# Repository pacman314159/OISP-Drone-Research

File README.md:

# 🚁 OISP Drone Research — Master Technical & System Architecture Document

> **Target Hardware Platform**: Custom Quadcopter UAV (ESP32-S3 WROOM-1 Dual-Core @ 240 MHz running FreeRTOS / ESP-IDF)  
> **Core Architecture Specs**: Hard Real-Time 500 Hz IMU Control Loop, Cascaded PID, EKF State Estimation, Zero Dynamic Allocation inside Flight Loops.  
> **Repository Location**: [d:/OneDrive_MSFT/Work/Drone_Research](file:///d:/OneDrive_MSFT/Work/Drone_Research)

---

## 📑 Master Table of Contents
- [1. Chapter 1: System Life Cycle & Finite State Machines (FSM)](#1-chapter-1-system-life-cycle--finite-state-machines-fsm)
  - [1.1 System Life Cycle Overview](#11-system-life-cycle-overview)
  - [1.2 State Transition Event Matrix](#12-state-transition-event-matrix)
  - [1.3 FSM Firmware File Registry](#13-fsm-firmware-file-registry)
  - [1.4 FSM State to RTOS Task Lifecycle Mapping](#14-fsm-state-to-rtos-task-lifecycle-mapping)
- [2. Chapter 2: Real-Time Operating System (RTOS) Architecture](#2-chapter-2-real-time-operating-system-rtos-architecture)
  - [2.1 Task Registry, Core Allocation & Priorities](#21-task-registry-core-allocation--priorities)
  - [2.2 Inter-Task Synchronization & Inter-Process Communication (IPC)](#22-inter-task-synchronization--inter-process-communication-ipc)
  - [2.3 Data Pipeline & Shared Resource Flow Diagram](#23-data-pipeline--shared-resource-flow-diagram)
  - [2.4 Shared Resource Storage & Firmware Declaration Registry](#24-shared-resource-storage--firmware-declaration-registry)
  - [2.5 Step-by-Step Task Function Execution Sequences](#25-step-by-step-task-function-execution-sequences)
- [3. Chapter 3: Firmware Architecture](#3-chapter-3-firmware-architecture)
  - [3.1 Layered Architecture Overview](#31-layered-architecture-overview)
  - [3.2 Cross-Layer Correlation & Interface Contracts](#32-cross-layer-correlation--interface-contracts)
  - [3.3 Firmware Directory & Module Registry](#33-firmware-directory--module-registry)
- [4. Chapter 4: Control System & Dynamics Architecture](#4-chapter-4-control-system--dynamics-architecture)
  - [4.1 6-DOF Quadcopter Physical Kinematics & Dynamics](#41-6-dof-quadcopter-physical-kinematics--dynamics)
  - [4.2 Mass Properties & Moment of Inertia Matrix](#42-mass-properties--moment-of-inertia-matrix)
  - [4.3 Cascaded PID Control Loop Architecture](#43-cascaded-pid-control-loop-architecture)
  - [4.4 State Estimation & Extended Kalman Filter (EKF)](#44-state-estimation--extended-kalman-filter-ekf)
  - [4.5 Control System Codebase Location Registry](#45-control-system-codebase-location-registry)
- [5. Master Cross-System Traceability Matrix](#5-master-cross-system-traceability-matrix)

---

## 1. Chapter 1: System Life Cycle & Finite State Machines (FSM)

### 1.1 System Life Cycle Overview
The operational lifecycle of the UAV from power-on until system termination is governed by a hierarchical Finite State Machine (FSM).

```mermaid
stateDiagram-v2
    [*] --> POWER_ON
    POWER_ON --> BOOT_INIT: Power Applied / Reset
    BOOT_INIT --> SENSOR_CALIBRATION: Hardware Self-Test Pass
    BOOT_INIT --> SYSTEM_ERROR: Self-Test Fail
    SENSOR_CALIBRATION --> DISARMED: Gyro/Mag Calibrated & Gyro Bias Saved
    SENSOR_CALIBRATION --> SYSTEM_ERROR: Calib Timeout / Sensor Fault
    
    state DISARMED {
        [*] --> IDLE_STANDBY
        IDLE_STANDBY --> ARMING_CHECKS: Arm Command Received (RC/GCS)
        ARMING_CHECKS --> READY_TO_ARM: All Pre-flight Checks Pass
        ARMING_CHECKS --> IDLE_STANDBY: Pre-flight Check Fail
    }
    
    DISARMED --> ARMED: Switch to ARMED State
    
    state ARMED {
        [*] --> MOTOR_SPINUP
        MOTOR_SPINUP --> IN_FLIGHT: Throttle > Min Takeoff Threshold
        IN_FLIGHT --> HOVER: Position / Altitude Hold Active
        HOVER --> IN_FLIGHT: Trajectory / Manual Command Input
    }

    ARMED --> FAILSAFE: Lost RC / Battery Low / Attitude Angle > 60°
    FAILSAFE --> LANDING: Auto-Land Protocol Triggered
    LANDING --> DISARMED: Touchdown Detected (Accel Spikes + Zero Throttle)
    ARMED --> DISARMED: Disarm Command Received
    SYSTEM_ERROR --> [*]: Hard Lockup / Safety Shutdown
```

### 1.2 State Transition Event Matrix

| Current State | Next State | Trigger Event | Trigger Source | Condition / Safeguard |
| :--- | :--- | :--- | :--- | :--- |
| `POWER_ON` | `BOOT_INIT` | Hardware Reset / Power Up | Power Supply Unit | Microcontroller VDD stable @ 3.3V |
| `BOOT_INIT` | `SENSOR_CALIBRATION` | Peripherals Initialized | Internal SW (`main.cpp`) | I2C/SPI bus scan verified |
| `BOOT_INIT` | `SYSTEM_ERROR` | Peripheral Fail | Internal SW (`main.cpp`) | MPU6050 / BMP180 not responding |
| `SENSOR_CALIBRATION` | `DISARMED` | Calibration Complete | Internal SW (`sensor_task`) | Zero gyro drift, stationary surface |
| `DISARMED` | `ARMED` | ARM Switch toggled + Throttle Low | External HW (RC Transceiver) | Pitch/Roll centered, GPS Lock ok |
| `ARMED` | `FAILSAFE` | Signal Loss > 500ms or Low Voltage | External HW / Internal SW | Batt < 10.5V or RC Watchdog timeout |
| `FAILSAFE` | `LANDING` | Failsafe Timer Expired | Internal SW (`fsm_task`) | Descend rate controlled @ 0.5 m/s |
| `LANDING` | `DISARMED` | Ground Contact Detected | Internal SW (`estimator_task`) | Accel Z impact spike + Zero throttle |

### 1.3 FSM Firmware File Registry
- **FSM State Engine Source**: [`firmware/FC_v01/src/app/flight_fsm.cpp`](file:///d:/OneDrive_MSFT/Work/Drone_Research/firmware/FC_v01/src/app)
- **FSM Definitions Header**: [`firmware/FC_v01/include/app/flight_fsm.hpp`](file:///d:/OneDrive_MSFT/Work/Drone_Research/firmware/FC_v01/include/app)
- **State Enum Declarations**: `enum class FlightState : uint8_t { BOOT_INIT, SENSOR_CALIBRATION, DISARMED, ARMED, FAILSAFE, LANDING, SYSTEM_ERROR }`

### 1.4 FSM State to RTOS Task Lifecycle Mapping

| FSM State | Active Tasks (Spawned / Running) | Suspended / Terminated Tasks | Resource Access Rights |
| :--- | :--- | :--- | :--- |
| `BOOT_INIT` | `SystemInitTask` | `ImuTask`, `AttitudeTask`, `MotorControlTask` | SPI / I2C Bus Exclusive Lock |
| `SENSOR_CALIBRATION` | `SystemInitTask`, `ImuTask`, `TelemetryTask` | `MotorControlTask`, `AttitudeTask` | Dynamic Offset Recalibration Buffer |
| `DISARMED` | `ImuTask`, `AttitudeTask`, `TelemetryTask`, `BaroTask` | `MotorControlTask` | Read-only sensors, Motors PWM 0% |
| `ARMED` | `ImuTask`, `AttitudeTask`, `MotorControlTask`, `TelemetryTask` | None | Full Control Loop & PWM Motor Outputs |
| `FAILSAFE` | `ImuTask`, `AttitudeTask`, `MotorControlTask`, `FailsafeTask` | RC Parsing Task | Auto Nav / Fixed Decent Controller |
| `SYSTEM_ERROR` | `BlinkLedTask`, `TelemetryTask` | All Control & Motor Tasks | Emergency ESC Disable (PWM 0us) |

---

## 2. Chapter 2: Real-Time Operating System (RTOS) Architecture

### 2.1 Task Registry, Core Allocation & Priorities
The firmware executes under **FreeRTOS** on the dual-core **ESP32-S3** @ 240 MHz.

| Task Identifier | Core Pinning | Task Priority | Target Frequency | Stack Size | Function Pointer Location |
| :--- | :--- | :--- | :--- | :--- | :--- |
| `ImuTask` | Core 1 | 24 (Highest) | 500 Hz (2.0 ms) | 4096 bytes | [`firmware/FC_v01/src/app/tasks.cpp`](file:///d:/OneDrive_MSFT/Work/Drone_Research/firmware/FC_v01/src/app) |
| `AttitudeTask` | Core 1 | 22 | 250 Hz (4.0 ms) | 4096 bytes | [`firmware/FC_v01/src/app/tasks.cpp`](file:///d:/OneDrive_MSFT/Work/Drone_Research/firmware/FC_v01/src/app) |
| `MotorControlTask` | Core 1 | 20 | 500 Hz (2.0 ms) | 2048 bytes | [`firmware/FC_v01/src/app/tasks.cpp`](file:///d:/OneDrive_MSFT/Work/Drone_Research/firmware/FC_v01/src/app) |
| `BaroMagTask` | Core 0 | 10 | 50 Hz (20 ms) | 3072 bytes | [`firmware/FC_v01/src/app/tasks.cpp`](file:///d:/OneDrive_MSFT/Work/Drone_Research/firmware/FC_v01/src/app) |
| `TelemetryTask` | Core 0 | 5 | 20 Hz (50 ms) | 4096 bytes | [`firmware/FC_v01/src/telemetry/`](file:///d:/OneDrive_MSFT/Work/Drone_Research/firmware/FC_v01/src/telemetry) |

### 2.2 Inter-Task Synchronization & Inter-Process Communication (IPC)
- **Direct Task Notifications**: Used for high-speed zero-latency signaling from IMU ISR to `ImuTask`.
- **Mutexes**:
  - `g_i2c_bus_mutex`: Prevents concurrent bus collisions between `ImuTask` and `BaroMagTask`.
  - `g_state_mutex`: Guards access to global telemetry and system state structs.
- **Ring Buffers / Queues**:
  - `g_imu_queue`: Lock-free SCMC (Single Producer, Single Consumer) queue transferring 6-axis raw values to `AttitudeTask`.

### 2.3 Data Pipeline & Shared Resource Flow Diagram

```mermaid
flowchart TD
    subgraph Core1 ["Core 1: High-Speed Flight Control Loop (500 Hz / 250 Hz)"]
        HW_MPU["Hardware MPU6050 (I2C/SPI)"] -->|Interrupt ISR| TSK_IMU["ImuTask (500 Hz)"]
        TSK_IMU -->|Raw Accel/Gyro Data| BUF_IMU[("g_imu_data_buffer (Protected by RingBuffer)")]
        BUF_IMU --> TSK_ATT["AttitudeTask (250 Hz / Cascaded PID)"]
        TSK_ATT -->|Motor PWM Signals| HW_ESC["Hardware ESCs (MCPWM / RMT)"]
    end

    subgraph Core0 ["Core 0: Low-Priority Navigation & Telemetry (50 Hz / 20 Hz)"]
        HW_BMP["BMP180 Baro"] --> TSK_NAV["BaroMagTask (50 Hz)"]
        TSK_NAV -->|Alt / Mag Data| BUF_NAV[("g_nav_data_buffer (Mutex: g_state_mutex)")]
        BUF_NAV --> TSK_TEL["TelemetryTask (20 Hz)"]
        TSK_TEL -->|Radio Packets| HW_RADIO["LoRa Ra-02 / NRF24L01+ / BLE"]
    end
```

### 2.4 Shared Resource Storage & Firmware Declaration Registry
- **Global Data Structures**: Defined in [`firmware/FC_v01/include/middleware/shared_resources.hpp`](file:///d:/OneDrive_MSFT/Work/Drone_Research/firmware/FC_v01/include/middleware)
- **Shared Variables**:
  - `IMUData g_imu_data; // Gyro (dps), Accel (m/s^2)`
  - `AttitudeData g_attitude; // Roll, Pitch, Yaw (radians)`
  - `MotorCommand g_motor_cmd; // PWM outputs (1000 - 2000 us)`
- **Zero Dynamic Memory Rule**: All mutexes (`StaticSemaphore_t`), queues (`xQueueCreateStatic`), and task stacks are statically instantiated at compile time.

### 2.5 Step-by-Step Task Function Execution Sequences

#### `ImuTask` Execution Flow (Loop Period: 2.0 ms)
1. **Step 1**: Block waiting for Direct Task Notification from MPU6050 INT pin ISR (`ulTaskNotifyTake`).
2. **Step 2**: Acquire `g_i2c_bus_mutex` with a 1 ms timeout.
3. **Step 3**: Execute burst read of 14 bytes from MPU6050 registers (Accel X, Y, Z, Temp, Gyro X, Y, Z).
4. **Step 4**: Release `g_i2c_bus_mutex`.
5. **Step 5**: Apply sensor calibration scale/offset matrices: $\mathbf{a}_{\text{corr}} = \mathbf{K}_a (\mathbf{a}_{\text{raw}} - \mathbf{b}_a)$.
6. **Step 6**: Push structured `IMUData` packet into `g_imu_queue` and unblock `AttitudeTask`.

---

## 3. Chapter 3: Firmware Architecture

### 3.1 Layered Architecture Overview
The firmware is structured into clean modular layers, adhering to strict single-direction dependency flows (Upper layers depend on lower layers, lower layers never include upper layers).

```
+-------------------------------------------------------------------+
| 5. Application Layer (flight_fsm, mission_manager, safety)        |
+-------------------------------------------------------------------+
| 4. Control Layer (cascaded_pid, rate_controller, attitude_ctrl)   |
+-------------------------------------------------------------------+
| 3. Estimator Layer (ekf_sensor_fusion, complementary_filter)      |
+-------------------------------------------------------------------+
| 2. Middleware Layer (shared_resources, ring_buffer, rtos_wrappers)|
+-------------------------------------------------------------------+
| 1. Drivers & Platform HAL (mpu6050, bmp180, i2c_master, mcpwm)     |
+-------------------------------------------------------------------+
```

### 3.2 Cross-Layer Correlation & Interface Contracts

| Driver Module | Platform HAL Interface | Upper Middleware Data Producer | Consuming Control Module |
| :--- | :--- | :--- | :--- |
| `mpu6050_driver.cpp` | `esp_i2c_master.c` | `g_imu_queue` | `cascaded_pid.cpp` |
| `bmp180_driver.cpp` | `esp_i2c_master.c` | `g_baro_queue` | `altitude_kalman.cpp` |
| `esc_driver.cpp` | `esp_mcpwm_hal.c` | `g_motor_cmd` | Direct Hardware Actuators |
| `lora_ra02_driver.cpp`| `esp_spi_master.c` | `g_telemetry_queue` | `ground_station_link.cpp` |

### 3.3 Firmware Directory & Module Registry
- **Root Firmware Directory**: [`firmware/FC_v01/`](file:///d:/OneDrive_MSFT/Work/Drone_Research/firmware/FC_v01)
  - `src/app/`: Application state logic and RTOS task definitions.
  - `src/control/`: Inner-loop rate PID, outer-loop attitude PID implementations.
  - `src/estimators/`: EKF 9-DOF / 6-DOF sensor fusion state estimation.
  - `src/drivers/`: Hardware driver implementations for MPU6050, BMP180, HMC5883L, ESC PWM.
  - `src/platforms/`: ESP32-S3 ESP-IDF peripheral hardware abstraction wrapper layer.
  - `src/middleware/`: RTOS IPC primitives, ring buffers, and thread-safe data accessors.

---

## 4. Chapter 4: Control System & Dynamics Architecture

### 4.1 6-DOF Quadcopter Physical Kinematics & Dynamics
The flight dynamics are modeled using 6-DOF rigid body Newton-Euler equations expressed in the Body Frame $B$ relative to the Inertial Earth Frame $N$.

$$\begin{aligned}
\dot{\mathbf{p}}^N &= \mathbf{v}^N \\
\dot{\mathbf{v}}^N &= \frac{1}{m} \mathbf{R}_B^N \mathbf{F}^B - \begin{bmatrix} 0 \\ 0 \\ g \end{bmatrix} \\
\dot{\mathbf{R}}_B^N &= \mathbf{R}_B^N \boldsymbol{\Omega}_\times \\
\mathbf{I} \dot{\boldsymbol{\omega}}^B &= \boldsymbol{\tau}^B - \boldsymbol{\omega}^B \times (\mathbf{I} \boldsymbol{\omega}^B)
\end{aligned}$$

Where:
- $\mathbf{p}^N = [x, y, z]^T$: Inertial position (m)
- $\mathbf{v}^N = [v_x, v_y, v_z]^T$: Velocity vector (m/s)
- $\mathbf{R}_B^N$: Rotation matrix from Body frame to Earth frame
- $\boldsymbol{\omega}^B = [p, q, r]^T$: Body angular rates (rad/s)
- $\mathbf{F}^B = [0, 0, \sum T_i]^T$: Total thrust generated by BLDC motors (N)
- $\boldsymbol{\tau}^B = [\tau_\phi, \tau_\theta, \tau_\psi]^T$: Roll, Pitch, and Yaw moments (N·m)

### 4.2 Mass Properties & Moment of Inertia Matrix
Derived from CAD model assemblies ([`3d_models/Full_body/`](file:///d:/OneDrive_MSFT/Work/Drone_Research/3d_models/Full_body)):

$$\mathbf{I} = \begin{bmatrix} I_{xx} & 0 & 0 \\ 0 & I_{yy} & 0 \\ 0 & 0 & I_{zz} \end{bmatrix} = \begin{bmatrix} 0.0142 & 0 & 0 \\ 0 & 0.0142 & 0 \\ 0 & 0 & 0.0285 \end{bmatrix} \text{kg}\cdot\text{m}^2$$

### 4.3 Cascaded PID Control Loop Architecture

```mermaid
flowchart LR
    SP["Desired Attitude (Roll, Pitch, Yaw)"] --> SUM1(("+"))
    SUM1 -->|Angle Error| PID_ANG["Angle PID Controller (100 Hz)"]
    PID_ANG -->|Desired Angular Rate| SUM2(("+"))
    IMU_ATT["Attitude Estimator (EKF / Complementary)"] -->|"-"| SUM1
    
    SUM2 -->|Rate Error| PID_RATE["Rate PID Controller (500 Hz)"]
    IMU_GYRO["IMU Gyroscope (500 Hz)"] -->|"-"| SUM2
    
    PID_RATE -->|Control Torque τ| MIXER["Motor Mixer Matrix"]
    MIXER -->|Motor Speeds ω1..4| ESC["ESC / BLDC Motors"]
```

#### Motor Control Mixer Equation ($X$-Configuration Quadcopter)
$$\begin{bmatrix} u_1 \\ u_2 \\ u_3 \\ u_4 \end{bmatrix} = \begin{bmatrix} 1 & -1 & 1 & 1 \\ 1 & -1 & -1 & -1 \\ 1 & 1 & -1 & 1 \\ 1 & 1 & 1 & -1 \end{bmatrix} \begin{bmatrix} T_{\text{coll}} \\ \tau_\phi \\ \tau_\theta \\ \tau_\psi \end{bmatrix}$$

### 4.4 State Estimation & Extended Kalman Filter (EKF)
State Vector ($\mathbf{x} \in \mathbb{R}^7$):
$$\mathbf{x} = \begin{bmatrix} q_0 & q_1 & q_2 & q_3 & b_{gx} & b_{gy} & b_{gz} \end{bmatrix}^T$$

- **Predict Step**: $\hat{\mathbf{x}}_{k|k-1} = f(\hat{\mathbf{x}}_{k-1}, \mathbf{u}_k)$
- **Covariance Predict**: $\mathbf{P}_{k|k-1} = \mathbf{F}_k \mathbf{P}_{k-1} \mathbf{F}_k^T + \mathbf{Q}_k$
- **Kalman Gain**: $\mathbf{K}_k = \mathbf{P}_{k|k-1} \mathbf{H}_k^T (\mathbf{H}_k \mathbf{P}_{k|k-1} \mathbf{H}_k^T + \mathbf{R}_k)^{-1}$
- **Update Step**: $\hat{\mathbf{x}}_{k|k} = \hat{\mathbf{x}}_{k|k-1} + \mathbf{K}_k (\mathbf{z}_k - h(\hat{\mathbf{x}}_{k|k-1}))$

### 4.5 Control System Codebase Location Registry
- **Cascaded PID Class**: [`firmware/FC_v01/src/control/cascaded_pid.cpp`](file:///d:/OneDrive_MSFT/Work/Drone_Research/firmware/FC_v01/src/control)
- **Motor Mixer Matrix**: [`firmware/FC_v01/src/control/motor_mixer.cpp`](file:///d:/OneDrive_MSFT/Work/Drone_Research/firmware/FC_v01/src/control)
- **EKF Math & Matrix Library**: [`firmware/EKF-sensor-fusion/test/EKF.cpp`](file:///d:/OneDrive_MSFT/Work/Drone_Research/firmware/EKF-sensor-fusion/test)
- **Signal Analyzers (Python)**: [`analyzers/imu_fft.py`](file:///d:/OneDrive_MSFT/Work/Drone_Research/analyzers)

---

## 5. Master Cross-System Traceability Matrix

This matrix establishes unambiguous links across FSM States, RTOS Tasks, Firmware Modules, Data Buffers, and Control/Physics Formulations.

| FSM State ID | Active RTOS Task | Firmware Layer & Path | Shared Resource / Buffer | Math / Physics Reference |
| :--- | :--- | :--- | :--- | :--- |
| `BOOT_INIT` | `SystemInitTask` | [`src/app/main.cpp`](file:///d:/OneDrive_MSFT/Work/Drone_Research/firmware/FC_v01/src/main.cpp) | `g_i2c_bus_mutex` | Hardware Register Specs |
| `SENSOR_CALIBRATION` | `ImuTask` | [`src/drivers/mpu6050.cpp`](file:///d:/OneDrive_MSFT/Work/Drone_Research/firmware/FC_v01/src/drivers) | `g_imu_calib_buffer` | Accel/Gyro Bias $\mathbf{b}_a, \mathbf{b}_g$ |
| `DISARMED` | `BaroMagTask` | [`src/drivers/bmp180.cpp`](file:///d:/OneDrive_MSFT/Work/Drone_Research/firmware/FC_v01/src/drivers) | `g_nav_data_buffer` | Barometric Formula $h = f(P)$ |
| `ARMED` | `ImuTask` (500Hz) | [`src/app/tasks.cpp`](file:///d:/OneDrive_MSFT/Work/Drone_Research/firmware/FC_v01/src/app) | `g_imu_queue` | Rate Loop Gyro $\boldsymbol{\omega}^B$ |
| `ARMED` | `AttitudeTask` (250Hz)| [`src/control/cascaded_pid.cpp`](file:///d:/OneDrive_MSFT/Work/Drone_Research/firmware/FC_v01/src/control) | `g_motor_cmd` | Cascaded PID & Mixer Matrix |
| `FAILSAFE` | `FailsafeTask` | [`src/app/flight_fsm.cpp`](file:///d:/OneDrive_MSFT/Work/Drone_Research/firmware/FC_v01/src/app) | `g_failsafe_state` | Descent Dynamics $\dot{z} = -0.5\text{m/s}$ |

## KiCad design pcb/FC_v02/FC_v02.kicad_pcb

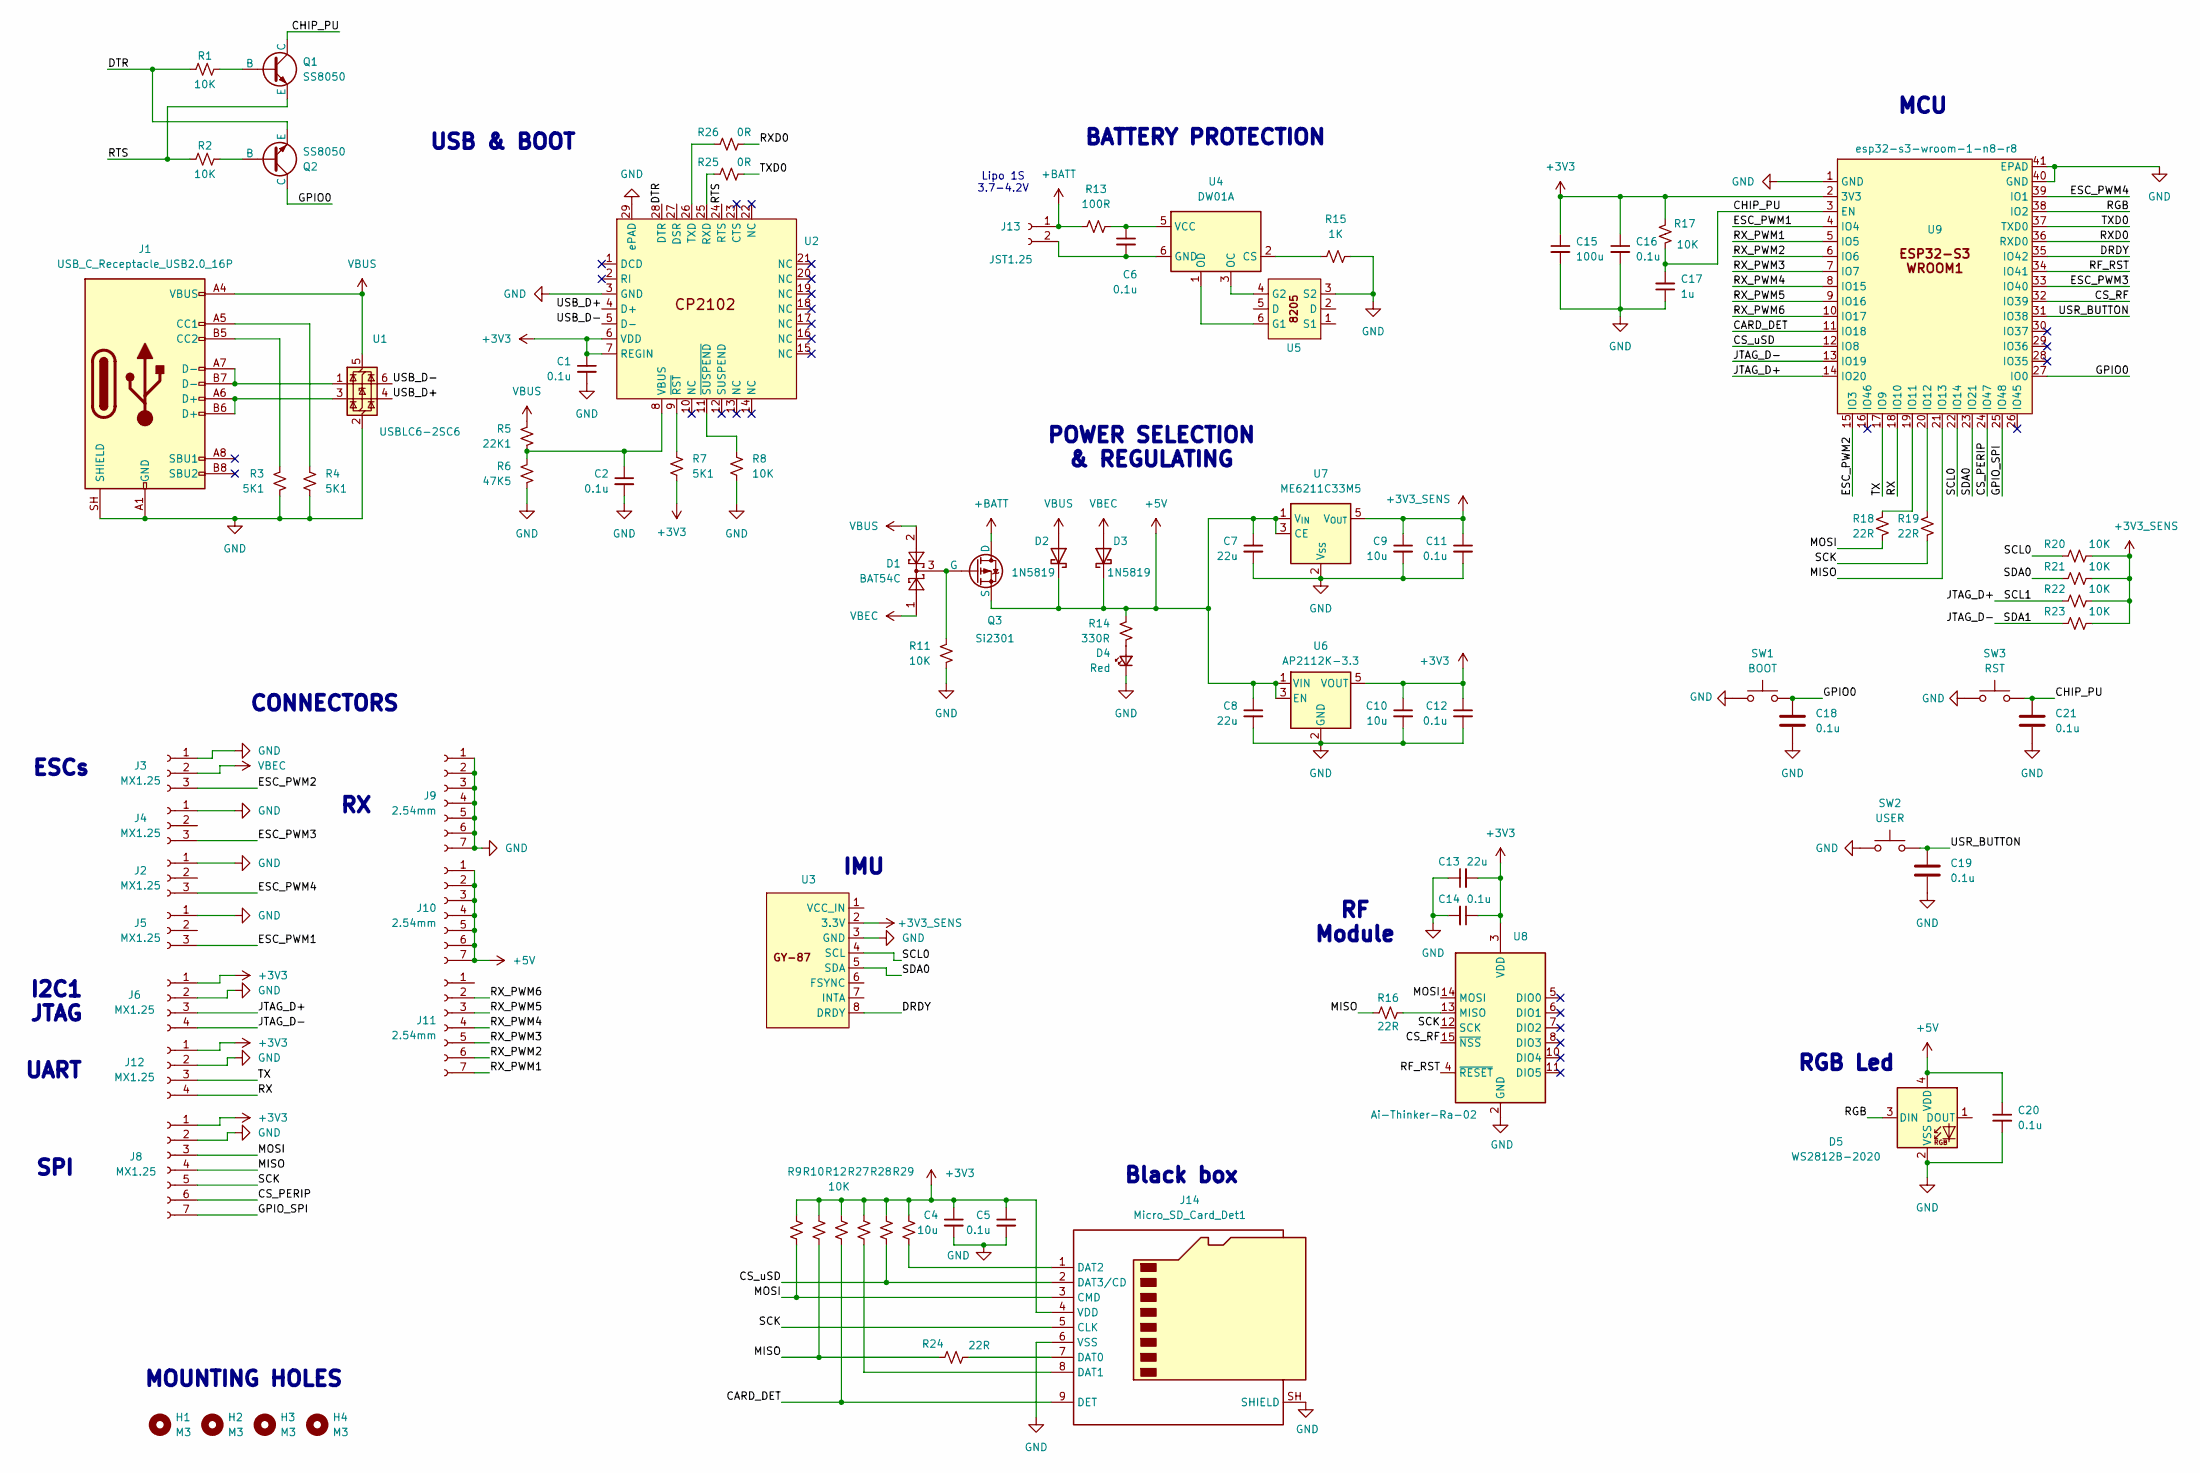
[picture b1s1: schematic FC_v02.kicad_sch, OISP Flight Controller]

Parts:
C1, C2, C5, C6, C11, C12, C14, C16, C18, C19, C20, C21: 0.1u; C_0603_1608Metric
C4, C9, C10: 10u; C_0805_2012Metric
C7, C8: 22u; CP_EIA-3216-10_Kemet-I
C13: 22u; C_0805_2012Metric
C15: 100u; CP_EIA-3216-10_Kemet-I
C17: 1u; C_0603_1608Metric
D1: BAT54C; SOT-23
D2, D3: 1N5819; D_SOD-123
D4: Red; LED_0805_2012Metric
D5: WS2812B-2020; LED_WS2812B-2020_PLCC4_2.0x2.0mm
H1, H2, H3, H4: M3; MountingHole_3.2mm_M3_DIN965_Pad
J1: USB_C_Receptacle_USB2.0_16P; USB_C_Receptacle_GCT_USB4105-xx-A_16P_TopMnt_Horizontal
J2, J3, J4, J5: MX1.25; MX_1.25mm_RA_SMD_3P
J6, J12: MX1.25; MX_1.25mm_RA_SMD_4P
J8: MX1.25; MX_1.25mm_RA_SMD_8P
J9, J10, J11: 2.54mm; _PinSocket_1x07_P2.54mm_Vertical
J13: JST1.25; MX_1.25mm_RA_SMD_2P
J14: Micro_SD_Card_Det1; Micro_SD_Card_Socket
Q1, Q2: SS8050; SOT-23
Q3: Si2301; SOT-23
R1, R2, R8, R9, R10, R11, R12, R17, R20, R21, R22, R23, R27, R28, R29: 10K; R_0603_1608Metric
R3, R4, R7: 5K1; R_0603_1608Metric
R5: 22K1; R_0603_1608Metric
R6: 47K5; R_0603_1608Metric
R13: 100R; R_0603_1608Metric
R14: 330R; R_0603_1608Metric
R15: 1K; R_0603_1608Metric
R16, R18, R19, R24: 22R; R_0603_1608Metric
R25, R26: 0R; R_0603_1608Metric
SW1: BOOT; SW_Push_3x4x2.5mm
SW2: USER; SW_Push_3x4x2.5mm
SW3: RST; SW_Push_3x4x2.5mm
U1: USBLC6-2SC6; SOT-23-6
U2: CP2102; QFN-28-1EP_5x5mm_P0.5mm_EP3.25x3.25mm_ThermalVias
U3: GY-87
U4: DW01A; SOT-23-6
U5: 8205; TSOT-23-6
U6: AP2112K-3.3; SOT-23-5
U7: ME6211C33M5; SOT-23-5
U8: Ai-Thinker-Ra-02; Ai-Thinker-Ra-01-LoRa
U9: esp32-s3-wroom-1-n8-r8; ESP32-S3-WROOM-1

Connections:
+3V3: C1.1, C4.1, C5.1, C10.1, C12.1, C13.2, C14.1, C15.1, C16.1, J6.1, J8.1, J12.1, J14.4 (VDD), R7.2, R9.1, R10.1, R12.1, R17.1, R27.1, R28.1, R29.1, U2.6 (VDD), U2.7 (REGIN), U6.5 (VOUT), U8.3 (VDD), U9.2 (3V3)
+3V3_SENS: C9.1, C11.1, R20.2, R21.2, R22.2, R23.2, U3.2 (3.3V), U7.5 (V_{OUT})
+5V: C7.1, C8.1, C20.1, D2.1 (K), D3.1 (K), D5.4 (VDD), J10.1, J10.2, J10.3, J10.4, J10.5, J10.6, J10.7, Q3.2 (S), R14.2, U6.1 (VIN), U6.3 (EN), U7.1 (V_{IN}), U7.3 (CE)
+BATT: J13.1, Q3.3 (D), R13.1
/CARD_DET: J14.9 (DET), R12.2, U9.11 (IO18)
/CHIP_PU: C17.2, C21.1, Q1.3 (C), R17.2, SW3.2, U9.3 (EN)
/CS_PERIP: J8.6, U9.24 (IO47)
/CS_RF: U8.15 (~NSS), U9.32 (IO39)
/CS_uSD: J14.2 (DAT3/CD), R28.2, U9.12 (IO8)
/DRDY: U3.8 (DRDY), U9.35 (IO42)
/DTR: Q2.2 (E), R1.1, U2.28 (DTR)
/ESC_PWM1: J5.3, U9.4 (IO4)
/ESC_PWM2: J3.3, U9.15 (IO3)
/ESC_PWM3: J4.3, U9.33 (IO40)
/ESC_PWM4: J2.3, U9.39 (IO1)
/GPIO0: C18.1, Q2.3 (C), SW1.2, U9.27 (IO0)
/GPIO_SPI: J8.7, U9.25 (IO48)
/JTAG_D+: J6.3, R22.1, U9.14 (IO20)
/JTAG_D-: J6.4, R23.1, U9.13 (IO19)
/MISO: J8.4, R10.2, R16.1, R24.1, U9.21 (IO13)
/MOSI: J8.3, J14.3 (CMD), R9.2, R18.2, U8.14 (MOSI)
/RF_RST: U8.4 (~RESET), U9.34 (IO41)
/RGB: D5.3 (DIN), U9.38 (IO2)
/RTS: Q1.2 (E), R2.1, U2.24 (RTS)
/RX: J12.4, U9.18 (IO10)
/RXD0: R26.2, U9.36 (RXD0)
/RX_PWM1: J11.7, U9.5 (IO5)
/RX_PWM2: J11.6, U9.6 (IO6)
/RX_PWM3: J11.5, U9.7 (IO7)
/RX_PWM4: J11.4, U9.8 (IO15)
/RX_PWM5: J11.3, U9.9 (IO16)
/RX_PWM6: J11.2, U9.10 (IO17)
/SCK: J8.5, J14.5 (CLK), R19.2, U8.12 (SCK)
/SCL0: R20.1, U3.4 (SCL), U9.22 (IO14)
/SDA0: R21.1, U3.5 (SDA), U9.23 (IO21)
/TX: J12.3, U9.17 (IO9)
/TXD0: R25.2, U9.37 (TXD0)
/USB_D+: U1.4 (I/O2), U2.4 (D+)
/USB_D-: U1.6 (I/O1), U2.5 (D-)
/USR_BUTTON: C19.1, SW2.2, U9.31 (IO38)
GND: C1.2, C2.2, C4.2, C5.2, C7.2, C8.2, C9.2, C10.2, C11.2, C12.2, C13.1, C14.2, C15.2, C16.2, C17.1, C18.2, C19.2, C20.2, C21.2, D4.1 (K), D5.2 (VSS), J1.A1 (GND), J1.A12 (GND), J1.B1 (GND), J1.B12 (GND), J1.SH (SHIELD), J2.1, J3.1, J4.1, J5.1, J6.2, J8.2, J9.1, J9.2, J9.3, J9.4, J9.5, J9.6, J9.7, J12.2, J14.6 (VSS), J14.SH (SHIELD), R3.2, R4.2, R6.2, R8.2, R11.1, R15.2, SW1.1, SW2.1, SW3.1, U1.2 (GND), U2.3 (GND), U2.29 (ePAD), U3.3 (GND), U5.3 (S2), U6.2 (GND), U7.2 (V_{SS}), U8.1 (GND), U8.2 (GND), U8.9 (GND), U8.16 (GND), U9.1 (GND), U9.40 (GND), U9.41 (EPAD)
unnamed: D4.2 (A), R14.1
unnamed: J1.A5 (CC1), R4.1
unnamed: J1.B5 (CC2), R3.1
unnamed: J1.A6 (D+), J1.B6 (D+), U1.3 (I/O2)
unnamed: J1.A7 (D-), J1.B7 (D-), U1.1 (I/O1)
unnamed: C6.2, J13.2, U4.6 (GND)
unnamed: J14.7 (DAT0), R24.2
unnamed: J14.8 (DAT1), R27.2
unnamed: J14.1 (DAT2), R29.2
unnamed: Q1.1 (B), R1.2
unnamed: Q2.1 (B), R2.2
unnamed: D1.3, Q3.1 (G), R11.2
unnamed: R25.1, U2.25 (RXD)
unnamed: R26.1, U2.26 (TXD)
unnamed: C2.1, R5.2, R6.1, U2.8 (VBUS)
unnamed: R7.1, U2.9 (~RST)
unnamed: R8.1, U2.11 (~SUSPEND)
unnamed: R15.1, U4.2 (CS)
unnamed: U4.3 (OC), U5.4 (G2)
unnamed: U4.1 (OD), U5.6 (G1)
unnamed: C6.1, R13.2, U4.5 (VCC)
unnamed: R16.2, U8.13 (MISO)
unnamed: R18.1, U9.19 (IO11)
unnamed: R19.1, U9.20 (IO12)
VBEC: D1.1, D3.2 (A), J3.2
VBUS: D1.2, D2.2 (A), J1.A4 (VBUS), J1.A9 (VBUS), J1.B4 (VBUS), J1.B9 (VBUS), R5.1, U1.5 (VBUS)

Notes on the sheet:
RF Module
ESCs
IMU
RGB Led
Black box
MCU
POWER SELECTION & REGULATING
USB & BOOT
Lipo 1S 3.7-4.2V
BATTERY PROTECTION
CONNECTORS
MOUNTING HOLES
SPI
I2C1 JTAG
UART

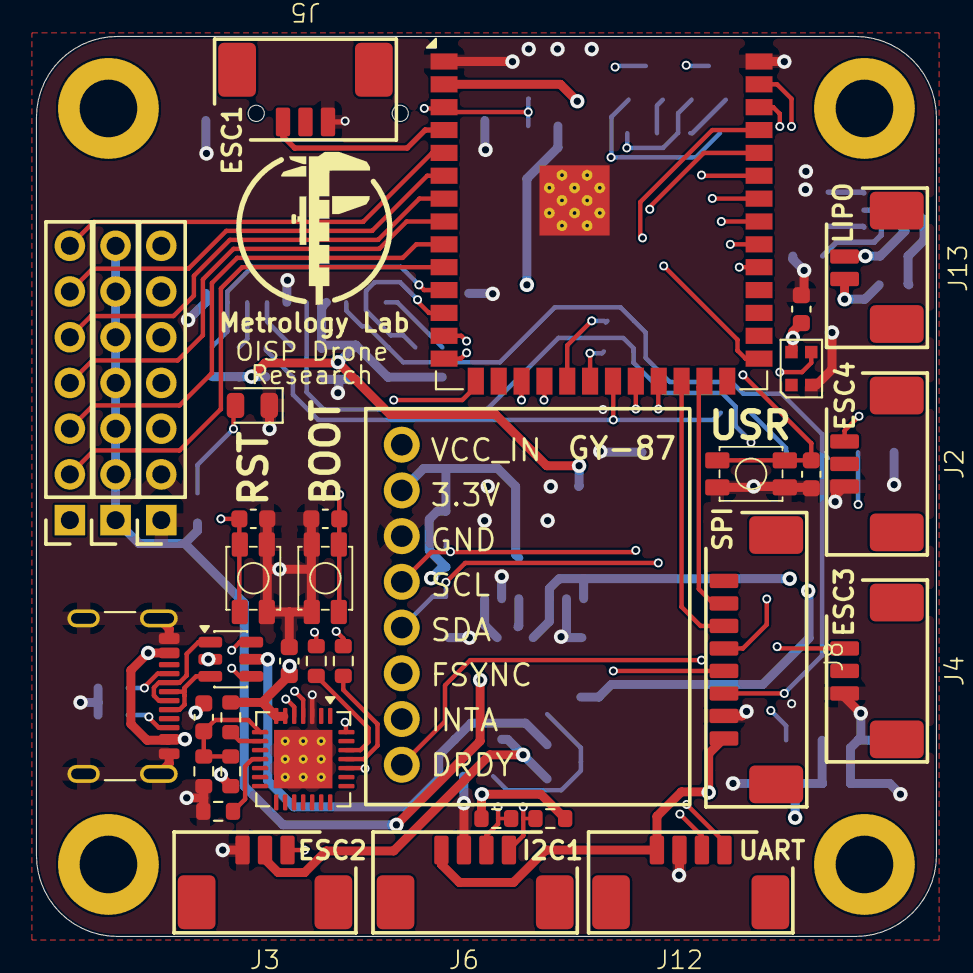
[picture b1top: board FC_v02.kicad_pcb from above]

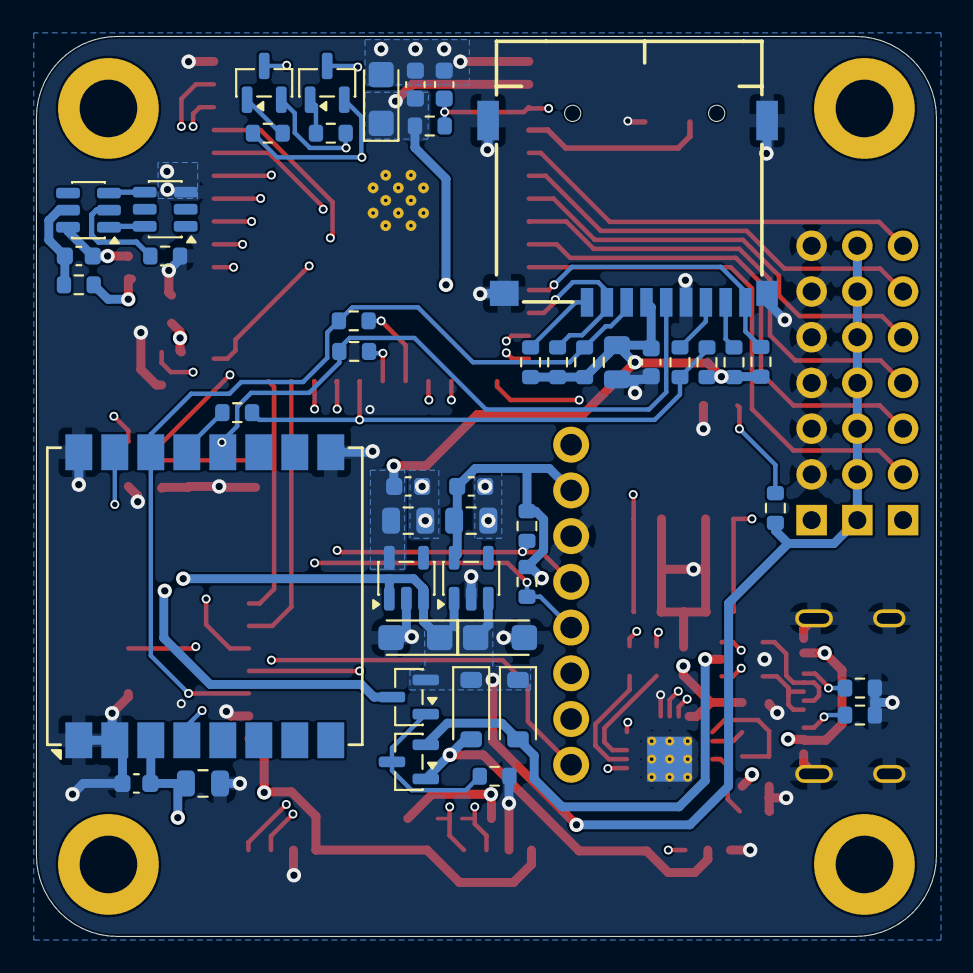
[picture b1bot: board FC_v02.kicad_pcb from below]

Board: 4 copper layers, 50.0 x 50.0 mm, 86 parts (47 on the bottom side), 67 nets.

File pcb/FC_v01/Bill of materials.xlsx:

Reference | Qty | Value | Footprint | Unit price | Unit total | Description | Supplier
C1 | 1 | 1u | Capacitor_SMD:C_0402_1005Metric
C2,C3,C5,C6,C11,C12,C14,C16,C18,C19,C20,C21 | 12 | 0.1u | Capacitor_SMD:C_0402_1005Metric
C4,C9,C10 | 3 | 10u | Capacitor_SMD:C_0805_2012Metric
C7,C8,C13 | 3 | 22u | Capacitor_SMD:C_0805_2012Metric
C15 | 1 | 100u | Capacitor_Tantalum_SMD:CP_EIA-3216-10_Kemet-I
C17 | 1 | 10u | Capacitor_SMD:C_0402_1005Metric
D4 | 1 | Red | LED_SMD:LED_0805_2012Metric
D5 | 1 | WS2812B-2020 | LED_SMD:LED_WS2812B-2020_PLCC4_2.0x2.0mm
J2,J3,J4,J5 | 4 | JST1.25 | Local Footprints:JST_1.25mm_RA_SMD_3P
J6,J12 | 2 | JST1.25 | Local Footprints:JST_1.25mm_RA_SMD_4P
J8 | 1 | JST1.25 | Local Footprints:JST_1.25mm_RA_SMD_8P
J9,J10,J11 | 3 | 2.54mm | Local Footprints:_PinSocket_1x07_P2.54mm_Vertical
J13 | 1 | JST1.25 | Local Footprints:JST_1.25mm_RA_SMD_2P
J15 | 1 | JST1.25 | Connector_PinHeader_2.54mm:PinHeader_1x07_P2.54mm_Vertical
R1,R2,R8,R9,R10,R11,R17,R20,R21,R22,R23 | 11 | 10K | Resistor_SMD:R_0402_1005Metric
R3,R4 | 2 | 5K1 | Resistor_SMD:R_0402_1005Metric
R7 | 1 | 4K7 | Resistor_SMD:R_0402_1005Metric
R13 | 1 | 100 | Resistor_SMD:R_0402_1005Metric
R14 | 1 | 2K | Resistor_SMD:R_0402_1005Metric
R15 | 1 | 1K | Resistor_SMD:R_0402_1005Metric
R16,R18,R19,R24 | 4 | 22R | Resistor_SMD:R_0402_1005Metric
R25,R26 | 2 | 0R | Resistor_SMD:R_0402_1005Metric
SW1 | 1 | BOOT | Button_Switch_SMD:SW_SPST_EVQP2_MiddlePushTravel_H2.5mm
SW2 | 1 | USER | Button_Switch_SMD:SW_SPST_EVQP2_MiddlePushTravel_H2.5mm
SW3 | 1 | RST | Button_Switch_SMD:SW_SPST_EVQP2_MiddlePushTravel_H2.5mm
U2 | 1 | CP2102 | Package_DFN_QFN:QFN-28-1EP_5x5mm_P0.5mm_EP3.1x3.1mm
U3 | 1 | GY-87 | Local Footprints:GY-87
U8 | 1 | Ai-Thinker-Ra-02 | RF_Module:Ai-Thinker-Ra-01-LoRa
D1 | 1 | BAT54C | Package_TO_SOT_SMD:SOT-23 |  |  |  | https://chipn24.com/25-con-diode-schottky-dan-bat54c-kl3-sot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
RN1 | 1 | 10K | Resistor_SMD:R_Array_Concave_4x0603 |  |  |  | https://chipn24.com/25-con-tro-bang-0603x4-10k-0603-8p4r-id2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
R5 | 1 | 22K1 | Resistor_SMD:R_0402_1005Metric |  |  |  | https://chipn24.com/50-con-dien-tro-dan-smd-0402-22k-1-id10746.html
R6 | 1 | 47K5 | Resistor_SMD:R_0402_1005Metric |  |  |  | https://chipn24.com/50-con-dien-tro-dan-smd-0402-47k-1-id10754.html
J1 | 1 | USB_C_Receptacle_USB2.0_16P | Connector_USB:USB_C_Receptacle_GCT_USB4105-xx-A_16P_TopMnt_Horizontal |  |  |  | https://chipn24.com/dau-usb-type-c-v1-16p-usb-3-1-truyen-tai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
U5 | 1 | 8205 | Package_TO_SOT_SMD:TSOT-23-6 |  |  |  | https://chipn24.com/ic-dan-8205s-sot-23-6-smd-fs8205-8205-id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
U7 | 1 | ME6211C33M5 | Package_TO_SOT_SMD:SOT-23-5 |  |  |  | https://chipn24.com/ic-dan-me6211-sot23-5-smd-me6211c33m5g-n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
J14 | 1 | Micro_SD_Card_Det1 | Local Footprints:Micro_SD_Card_Socket |  |  |  | https://chipn24.com/socket-the-nho-microsd-v1-co-lo-xo-id1466.html
U9 | 1 | esp32s3_wroom1 | RF_Module:ESP32-S3-WROOM-1 |  |  |  | https://hshop.vn/mach-thu-phat-wifi-ble-soc-esp32-s3-esp32-s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
D2,D3 | 2 | 1N5819 | Diode_SMD:D_SOD-123 |  |  |  | https://icdayroi.com/diode-1n5819-sod123-size-1206
U1 | 1 | USBLC6-2SC6 | Package_TO_SOT_SMD:SOT-23-6 |  |  |  | https://icdayroi.com/usblc6-2sc6-tvs-diode-5-25v-17v-sot23-6
U6 | 1 | AP2112K-3.3 | Package_TO_SOT_SMD:SOT-23-5 |  |  |  | https://shopee.vn/Set-10-Linh-Ki%E1%BB%87n-%C4%90i%E1%BB%87n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
U4 | 1 | DW01A | Package_TO_SOT_SMD:SOT-23-6 |  |  |  | https://www.thegioiic.com/dw01a-ic-bao-ve-pin-1-cell-sot-23-6
Q3 | 1 | Si2301 | Package_TO_SOT_SMD:SOT-23 |  |  |  | https://www.thegioiic.com/si2301ds-mosfet-kenh-p-20v-2-3a-sot-23-3
Q1,Q2 | 2 | SS8050 | Package_TO_SOT_SMD:SOT-23 |  |  |  | https://www.thegioiic.com/ss8050-y1-transistor-npn-25v-1-5a-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

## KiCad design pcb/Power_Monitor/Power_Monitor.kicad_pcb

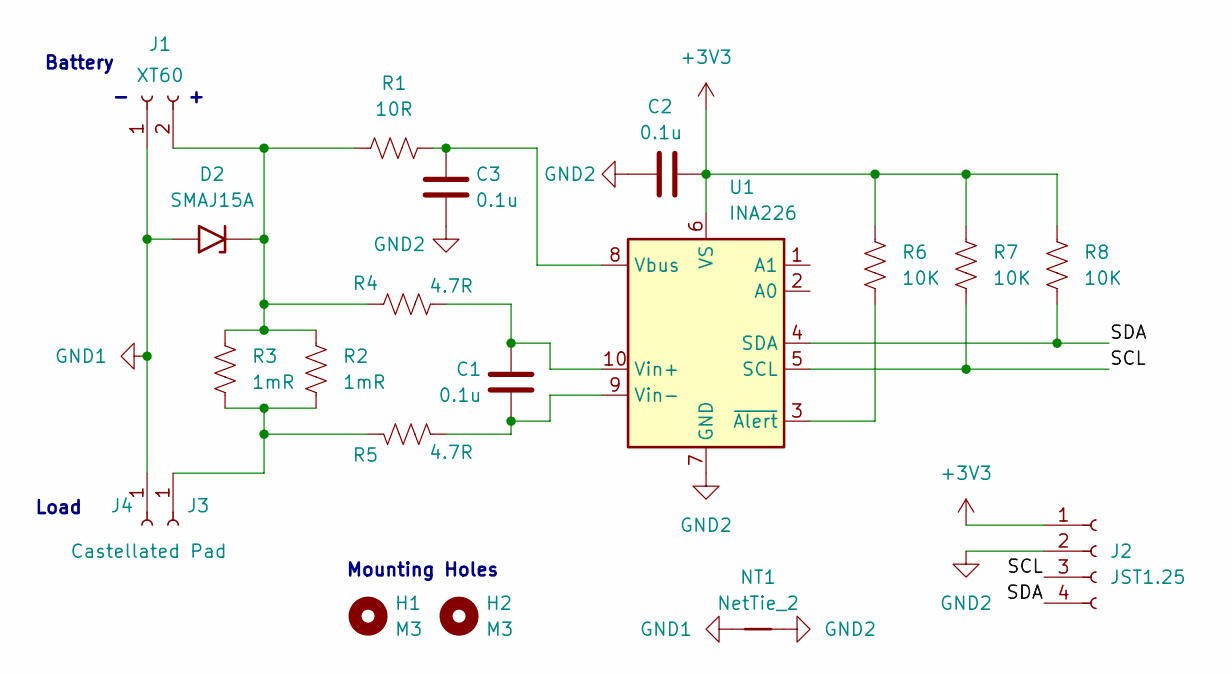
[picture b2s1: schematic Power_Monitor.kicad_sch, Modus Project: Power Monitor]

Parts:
C1, C2, C3: 0.1u; C_0402_1005Metric
D2: SMAJ15A; D_SMA
H1, H2: M3; MountingHole_3.2mm_M3_DIN965_Pad
J1: XT60; AMASS_XT60PW-M_1x02_P7.20mm_Horizontal
J2: JST1.25; JST_1.25mm_RA_SMD_4P
J3: Castellated Pad; Castellated_pad_high_side
J4: Castellated Pad; Castellated_pad_low_side
NT1: NetTie_2; NetTie-2_SMD_Pad0.5mm
R1: 10R; R_0402_1005Metric
R2, R3: 1mR; R_2512_6332Metric
R4, R5: 4.7R; R_0402_1005Metric
R6, R7, R8: 10K; R_0402_1005Metric
U1: INA226; TSSOP-10_3x3mm_P0.5mm

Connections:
+3V3: C2.1, J2.1, R6.2, R7.2, R8.2, U1.6 (VS)
/SCL: J2.3, R7.1, U1.5 (SCL)
/SDA: J2.4, R8.1, U1.4 (SDA)
GND1: D2.2 (A2), J1.1, J4.1 (Pin_1_1), NT1.1
GND2: C2.2, C3.2, J2.2, NT1.2, U1.7 (GND)
unnamed: D2.1 (A1), J1.2, R1.1, R2.1, R3.1, R4.1
unnamed: J3.1 (Pin_1_1), R2.2, R3.2, R5.1
unnamed: C3.1, R1.2, U1.8 (Vbus)
unnamed: C1.1, R4.2, U1.10 (Vin+)
unnamed: C1.2, R5.2, U1.9 (Vin-)
unnamed: R6.1, U1.3 (~Alert)

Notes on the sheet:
Mounting Holes
Load
Battery

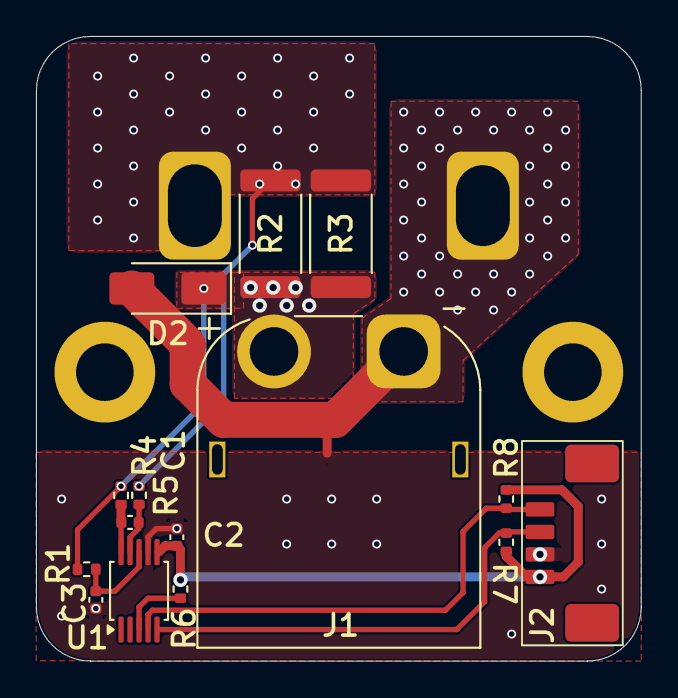
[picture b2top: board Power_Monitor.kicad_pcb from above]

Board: 2 copper layers, 33.6 x 34.7 mm, 20 parts (0 on the bottom side), 11 nets.

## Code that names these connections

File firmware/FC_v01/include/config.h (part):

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constexpr int IMU_SDA_PIN       = I2C0_SDA_PIN;

// ESC Motor PWM Output Pins
constexpr int ESC_PWM1_PIN      = 4;
constexpr int ESC_PWM2_PIN      = 3;
constexpr int ESC_PWM3_PIN      = 40;
constexpr int ESC_PWM4_PIN      = 1;

// ESC Motor PWM Hardware Settings (250 Hz Standard PWM, 1000-2000 us Pulse Width = 25-50% Duty Cycle)
constexpr uint8_t  MOTOR_COUNT                 = 4;
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constexpr int UART_RX_PIN       = 10;

// RC Receiver Input Pins
constexpr int RX_PWM1_PIN       = 5; // PPM
constexpr int RX_PWM2_PIN       = 6;
constexpr int RX_PWM3_PIN       = 7;
constexpr int RX_PWM4_PIN       = 15;
constexpr int RX_PWM5_PIN       = 16;
constexpr int RX_PWM6_PIN       = 17;

// Peripherals & User Interface Pins
constexpr int USER_BTN_PIN      = 38;
constexpr int LORA_RST_PIN      = 41;
constexpr int SD_CARD_DET_PIN   = 18;
constexpr int IMU_MAG_DRDY_PIN  = 42;
constexpr int RGB_LED_PIN       = 2;  // WS2812 Single RGB Status LED on PCB v02 (GPIO2)

// =============================================================================
// BUS & PERIPHERAL HARDWARE OPERATING CONFIGURATIONS
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
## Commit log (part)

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2026-04-20 First commit: intializing mgt resource
2026-04-20 Add placeholder files to track empty directories
2026-04-21 Add PCB files
2026-04-22 update pcb
2026-05-08 thrust testbench
2026-05-09 hello world
2026-05-09 Add sensor firmware and testing framework
    - Created platformio.ini for ESP32-S3 SuperMini configuration.
    - Implemented GY87_MPU6050 sensor class for MPU6050 functionality.
    - Developed main application to read data from MPU6050 and HMC5883L sensors.
    - Added README for test directory explaining unit testing with PlatformIO.
    - Implemented LED test to verify FastLED functionality.
    - Created I2C scanner to detect connected devices.
2026-05-09 Remove unused MPU6050 header and documentation files; update example code for MPU6050 usage
2026-05-09 Add MPU6050 and BMP085 sensor integration with I2C communication
    - Implemented main functionality for reading accelerometer, gyroscope, and barometric pressure data using MPU6050 and BMP085 sensors.
    - Added functions for I2C device probing, reading/writing registers, and calculating temperature and pressure.
    - Initialized sensors in the setup function and configured their settings.
    - Implemented a loop to continuously read and print sensor data at specified intervals.
    - Created a README file for the test directory to provide information on unit testing with PlatformIO.
2026-05-09 Add initial project structure and sensor integration for ESP32-S3
2026-05-10 Refactor MPU6050 integration: add raw data storage and update setup for data reading
2026-05-10 ccssc
2026-05-10 Add main test code for MPU6050 sensor integration
2026-05-10 Update MPU6050 example code: enhance comments and remove unused variable declarations
2026-05-12 Refactor MPU6050 integration: replace MPU6050_clone with GY87_MPU6050, update initialization and data retrieval methods, and add timing test functionality.
2026-06-03 analysis: fft and stdev bmp180
2026-06-03 schematic: battery and power selection
2026-06-03 add gitignore
2026-06-05 added footprints
2026-06-05 add footprints
2026-06-06 analyzer: imu distribution and fft
2026-06-06 integrate lib for hmc5883l
2026-06-11 lib for hmc5883l
2026-06-13 power rail splitting
2026-06-13 added gy87
2026-06-13 cat commit
2026-06-18 test commit
2026-06-19 (black box dont have footprint yet) (added rf module)
2026-06-20 hello
2026-06-20 allan deviation
2026-06-20 [analyze] finish mag with pin interrupt
2026-06-20 footprint
2026-06-21 add back example mpu6050
2026-06-21 9dof data aquisition example
2026-06-21 Add GY87 MPU6050 and HMC5883L sensor classes with I2C communication
    - Implemented GY87_MPU6050 class for MPU6050 sensor with methods for initialization, configuration, and data retrieval.
    - Implemented GY87_HMC5883L class for HMC5883L sensor with methods for initialization, configuration, and data retrieval.
    - Created main application file to demonstrate sensor data acquisition.
    - Added test files for unit testing of MPU6050 and HMC5883L sensors.
    - Included README files for project structure and testing guidelines.
    - Implemented I2C scanner for detecting connected devices.
2026-06-21 commit: Ra02-datasheet
